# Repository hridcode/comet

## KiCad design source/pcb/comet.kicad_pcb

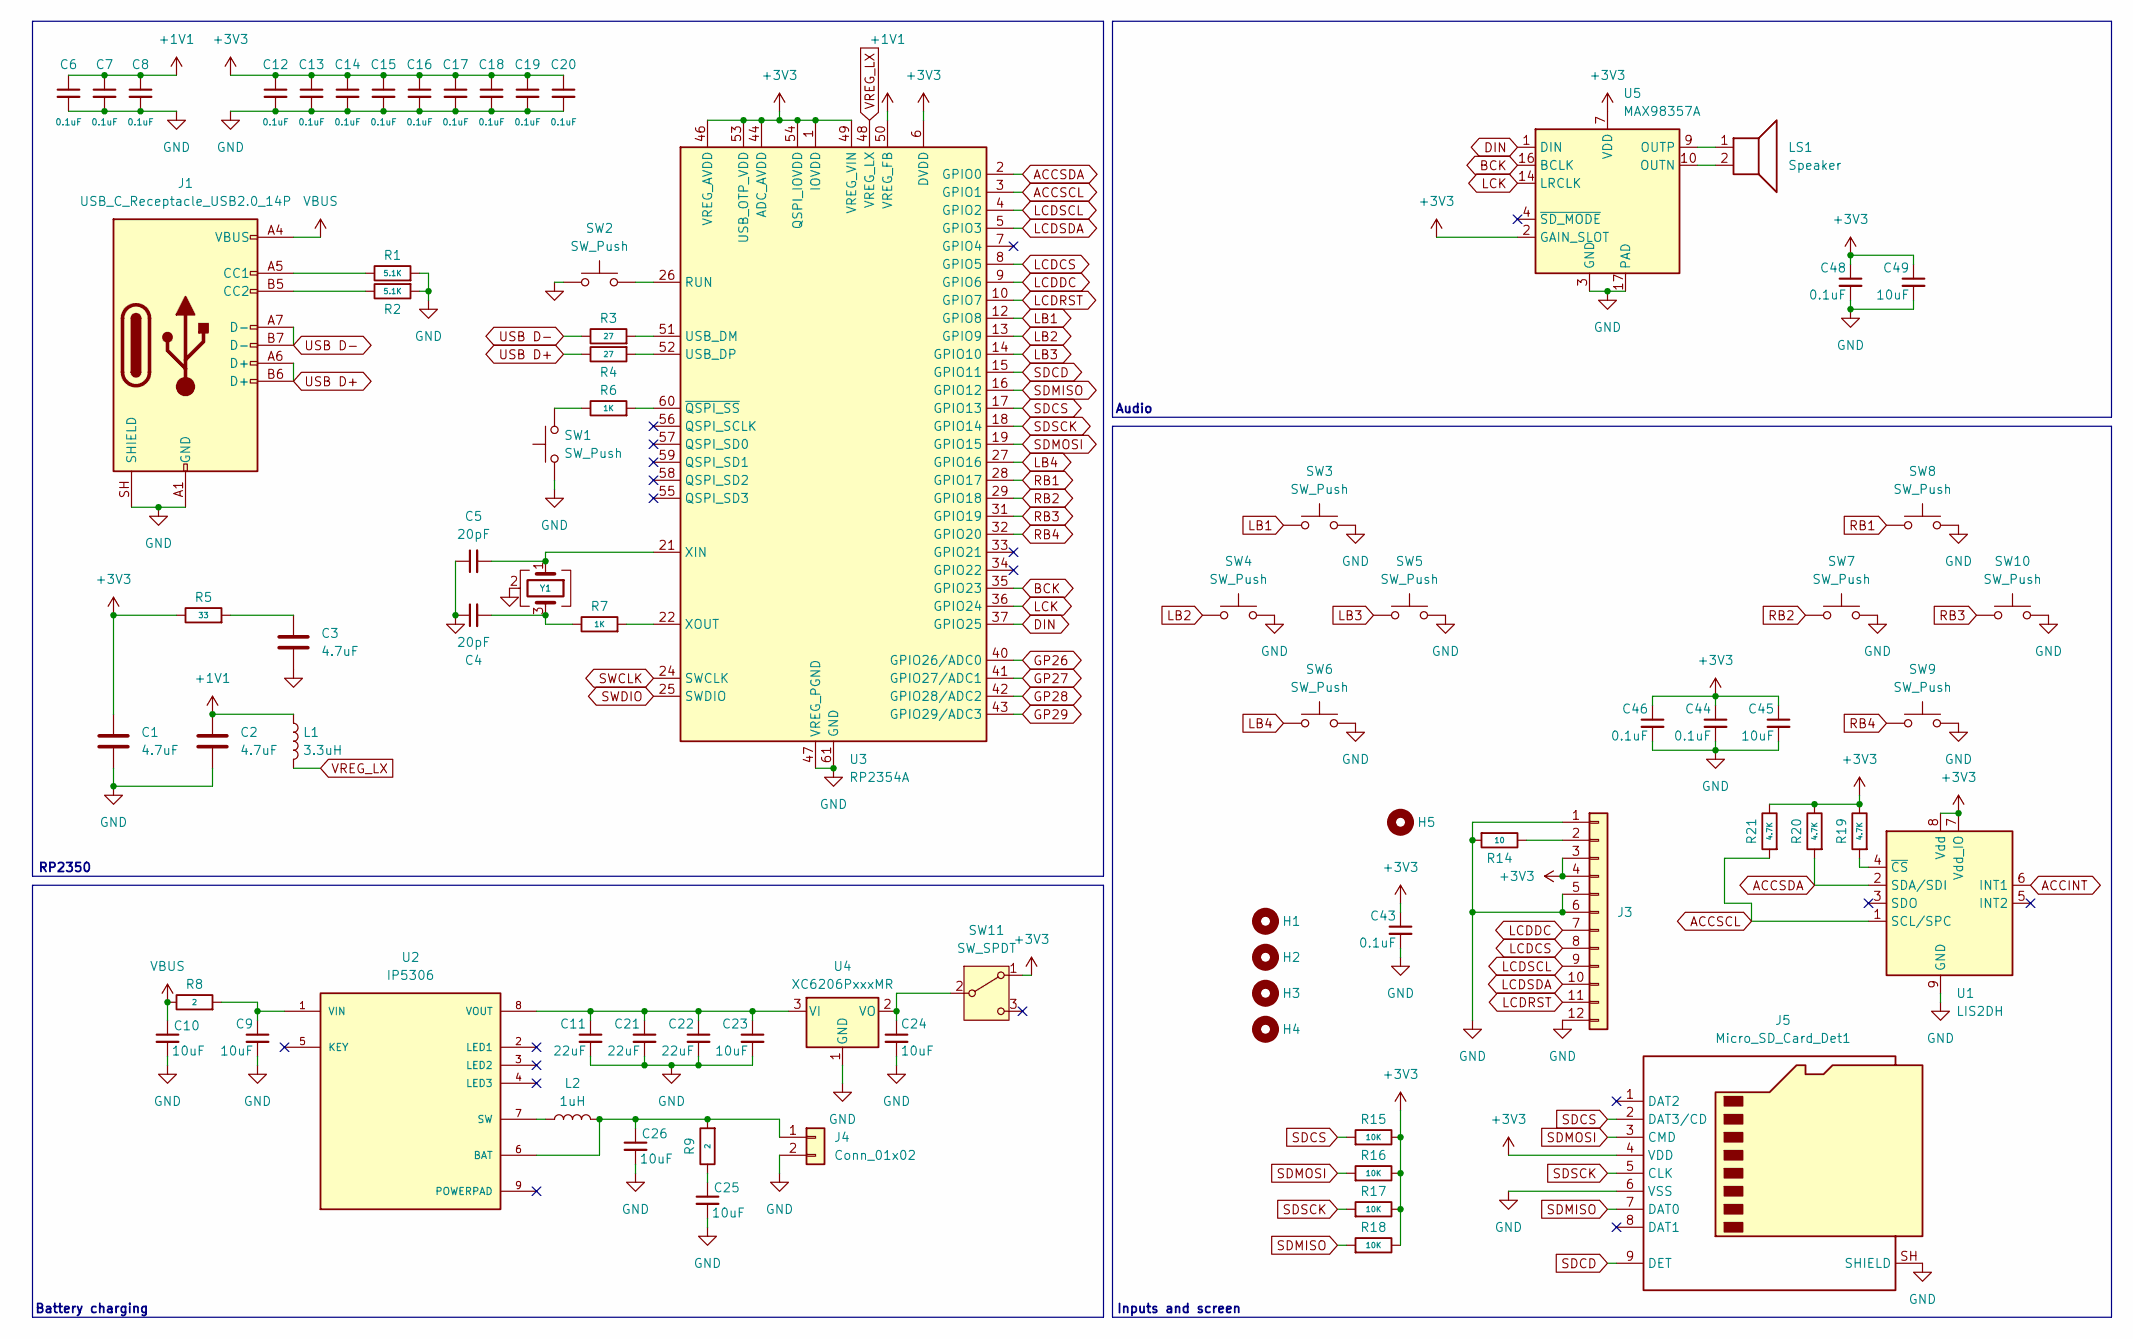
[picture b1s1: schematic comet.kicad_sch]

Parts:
C1, C2, C3: 4.7uF; C_0402_1005Metric; MPN C23733
C4, C5: 20pF; C_0402_1005Metric; MPN C1554
C6, C7, C8, C12, C13, C14, C15, C16, C17, C18, C19, C20: 0.1uF; C_0402_1005Metric; MPN C1525
C9, C10, C23, C24, C25, C26, C45, C49: 10uF; C_0402_1005Metric; MPN C15525
C11, C21, C22: 22uF; C_0603_1608Metric; MPN C59461
C43, C44, C46, C48: 0.1uF; C_0402_1005Metric; MPN C15525
H1, H2, H3, H4: MountingHole; MountingHole_3.2mm_M3
H5: MountingHole; display_hole
J1: USB_C_Receptacle_USB2.0_14P; USB_C_Receptacle_HRO_TYPE-C-31-M-12; MPN C165948
J3: Conn_01x12; Hirose_FH12-12S-0.5SH_1x12-1MP_P0.50mm_Horizontal
J4: Conn_01x02; PinHeader_1x02_P2.54mm_Vertical
J5: Micro_SD_Card_Det1; TF-SMD_TF-CARD-H1.8
L1: 3.3uH; L_0402_1005Metric; MPN C84474
L2: 1uH; L_0402_1005Metric; MPN C84468
LS1: Speaker; PinSocket_1x02_P2.54mm_Vertical
R1, R2: 5.1K; R_0402_1005Metric; MPN C25905
R3, R4: 27; R_0603_1608Metric; MPN C25190
R5: 33; R_0402_1005Metric; MPN C25105
R6, R7: 1K; R_0402_1005Metric; MPN C11702
R8, R9: 2; R_0603_1608Metric; MPN C22977
R14: 10; R_0402_1005Metric; MPN C11702
R15, R16, R17, R18: 10K; R_0402_1005Metric; MPN C11702
R19, R20, R21: 4.7K; R_0402_1005Metric; MPN C11702
SW1, SW2: SW_Push; L_Taiyo-Yuden_NR-40xx
SW3, SW4, SW5, SW6, SW7, SW8, SW9, SW10: SW_Push; SW-SMD_6x6
SW11: SW_SPDT; SW-TH_MSK12D18G2
U1: LIS2DH; LGA-14_2x2mm_P0.35mm_LayoutBorder3x4y
U2: IP5306; eSOP-8; PARTREV 1.31
U3: RP2354A; QFN-60-1EP_7x7mm_P0.4mm_EP3.4x3.4mm
U4: XC6206PxxxMR; SOT-23-3; MPN C5446
U5: MAX98357A; TQFN-16-1EP_3x3mm_P0.5mm_EP1.23x1.23mm
Y1: Crystal_GND24; Crystal_SMD_3225-4Pin_3.2x2.5mm; MPN C9002

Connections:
+1V1: C2.1, C6.1, C7.1, C8.1, L1.1, U3.50 (VREG_FB)
+3V3: C1.1, C12.1, C13.1, C14.1, C15.1, C16.1, C17.1, C18.1, C19.1, C20.1, C43.1, C44.1, C45.1, C46.1, C48.1, C49.1, J3.3, J3.4, J5.4 (VDD), R5.1, R15.1, R16.1, R17.1, R18.1, R19.1, R20.1, R21.1, SW11.1 (A), U1.7 (Vdd_IO), U1.8 (Vdd), U3.1 (IOVDD), U3.6 (DVDD), U3.11 (IOVDD), U3.20 (IOVDD), U3.23 (DVDD), U3.30 (IOVDD), U3.38 (IOVDD), U3.39 (DVDD), U3.44 (ADC_AVDD), U3.45 (IOVDD), U3.46 (VREG_AVDD), U3.49 (VREG_VIN), U3.53 (USB_OTP_VDD), U3.54 (QSPI_IOVDD), U5.2 (GAIN_SLOT), U5.7 (VDD), U5.8 (VDD)
ACCINT: U1.6 (INT1)
ACCSCL: R21.2, U1.1 (SCL/SPC), U3.3 (GPIO1)
ACCSDA: R20.2, U1.2 (SDA/SDI), U3.2 (GPIO0)
BCK: U3.35 (GPIO23), U5.16 (BCLK)
DIN: U3.37 (GPIO25), U5.1 (DIN)
GND: C1.2, C2.2, C3.2, C4.1, C5.1, C6.2, C7.2, C8.2, C9.2, C10.2, C11.2, C12.2, C13.2, C14.2, C15.2, C16.2, C17.2, C18.2, C19.2, C20.2, C21.2, C22.2, C23.2, C24.2, C25.2, C26.2, C43.2, C44.2, C45.2, C46.2, C48.2, C49.2, J1.A1 (GND), J1.A12 (GND), J1.B1 (GND), J1.B12 (GND), J1.SH (SHIELD), J3.1, J3.5, J3.6, J3.12, J4.2, J5.6 (VSS), J5.SH (SHIELD), R1.2, R2.2, R14.2, SW1.1, SW2.1, SW3.2, SW4.2, SW5.2, SW6.2, SW7.2, SW8.2, SW9.2, SW10.2, U1.9 (GND), U1.10 (GND), U1.11 (GND), U1.12 (GND), U1.13 (GND), U1.14 (GND), U3.47 (VREG_PGND), U3.61 (GND), U4.1 (GND), U5.3 (GND), U5.11 (GND), U5.15 (GND), U5.17 (PAD), Y1.2 (G), Y1.4 (G)
GP26: U3.40 (GPIO26/ADC0)
GP27: U3.41 (GPIO27/ADC1)
GP28: U3.42 (GPIO28/ADC2)
GP29: U3.43 (GPIO29/ADC3)
LB1: SW3.1, U3.12 (GPIO8)
LB2: SW4.1, U3.13 (GPIO9)
LB3: SW5.1, U3.14 (GPIO10)
LB4: SW6.1, U3.27 (GPIO16)
LCDCS: J3.8, U3.8 (GPIO5)
LCDDC: J3.7, U3.9 (GPIO6)
LCDRST: J3.11, U3.10 (GPIO7)
LCDSCL: J3.9, U3.4 (GPIO2)
LCDSDA: J3.10, U3.5 (GPIO3)
LCK: U3.36 (GPIO24), U5.14 (LRCLK)
unnamed: C3.1, R5.2
unnamed: C4.2, R7.1, Y1.3
unnamed: C25.1, R9.1
unnamed: J1.A5 (CC1), R1.1
unnamed: J1.B5 (CC2), R2.1
unnamed: J3.2, R14.1
unnamed: C26.1, J4.1, L2.2, R9.2, U2.6 (BAT)
unnamed: R6.1, SW1.2
unnamed: C24.1, SW11.2 (B), U4.2 (VO)
unnamed: R19.2, U1.4 (~CS)
unnamed: L2.1, U2.7 (SW)
unnamed: C9.1, R8.2, U2.1 (VIN)
unnamed: C11.1, C21.1, C22.1, C23.1, U2.8 (VOUT), U4.3 (VI)
unnamed: SW2.2, U3.26 (RUN)
unnamed: R3.2, U3.51 (USB_DM)
unnamed: R4.2, U3.52 (USB_DP)
unnamed: C5.2, U3.21 (XIN), Y1.1
unnamed: R7.2, U3.22 (XOUT)
unnamed: R6.2, U3.60 (~QSPI_SS)
unnamed: LS1.2, U5.10 (OUTN)
unnamed: LS1.1, U5.9 (OUTP)
RB1: SW8.1, U3.28 (GPIO17)
RB2: SW7.1, U3.29 (GPIO18)
RB3: SW10.1, U3.31 (GPIO19)
RB4: SW9.1, U3.32 (GPIO20)
SDCD: J5.9 (DET), U3.15 (GPIO11)
SDCS: J5.2 (DAT3/CD), R15.2, U3.17 (GPIO13)
SDMISO: J5.7 (DAT0), R18.2, U3.16 (GPIO12)
SDMOSI: J5.3 (CMD), R16.2, U3.19 (GPIO15)
SDSCK: J5.5 (CLK), R17.2, U3.18 (GPIO14)
SWCLK: U3.24 (SWCLK)
SWDIO: U3.25 (SWDIO)
USB D+: J1.A6 (D+), J1.B6 (D+), R4.1
USB D-: J1.A7 (D-), J1.B7 (D-), R3.1
VBUS: C10.1, J1.A4 (VBUS), J1.A9 (VBUS), J1.B4 (VBUS), J1.B9 (VBUS), R8.1
VREG_LX: L1.2, U3.48 (VREG_LX)

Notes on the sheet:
Battery charging
Audio
RP2350
Inputs and screen

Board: 2 copper layers, 78 parts (63 on the bottom side), 51 nets, no tracks yet.
